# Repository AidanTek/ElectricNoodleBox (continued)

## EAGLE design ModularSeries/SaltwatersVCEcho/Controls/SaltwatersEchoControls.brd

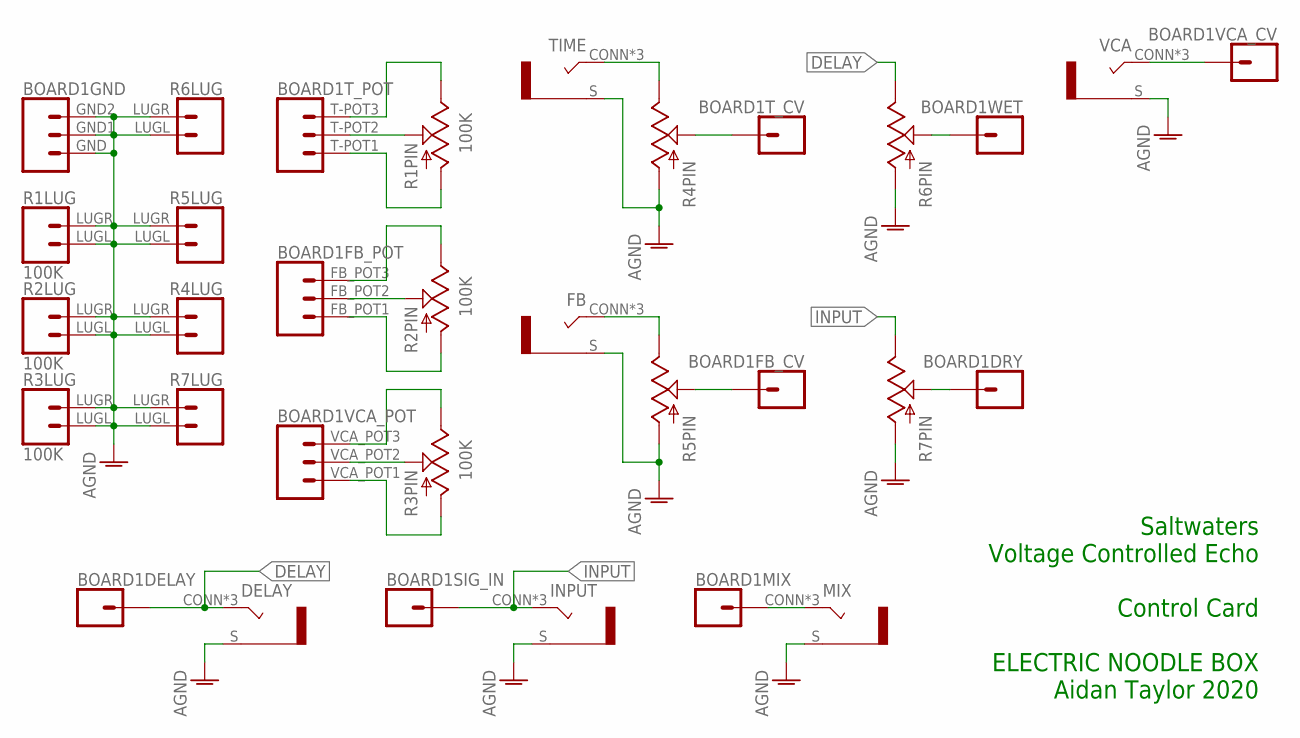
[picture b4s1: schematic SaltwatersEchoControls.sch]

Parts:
BOARD1: SALTWATERS_LINK; SALTWATERS
DELAY: COMBI-JACKCINCHNANA; NEWCOMBOJACK_PANEL
FB: COMBI-JACKCINCHNANA; NEWCOMBOJACK_PANEL
INPUT: COMBI-JACKCINCHNANA; NEWCOMBOJACK_PANEL
MIX: COMBI-JACKCINCHNANA; NEWCOMBOJACK_PANEL
R1, R2, R3: 100K; ALPHA_RV09_9MMPOT
R4, R5, R6, R7: POTENTIOMETER; ALPHA_RV09_9MMPOT
TIME: COMBI-JACKCINCHNANA; NEWCOMBOJACK_PANEL
VCA: COMBI-JACKCINCHNANA; NEWCOMBOJACK_PANEL

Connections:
AGND: BOARD1.GND (1), BOARD1.GND1 (2), BOARD1.GND2 (3), DELAY.S, FB.S, INPUT.S, MIX.S, R1.LUGL (1), R1.LUGR (2), R2.LUGL (1), R2.LUGR (2), R3.LUGL (1), R3.LUGR (2), R4.C1 (A), R4.LUGL (1), R4.LUGR (2), R5.C1 (A), R5.LUGL (1), R5.LUGR (2), R6.C1 (A), R6.LUGL (1), R6.LUGR (2), R7.C1 (A), R7.LUGL (1), R7.LUGR (2), TIME.S, VCA.S
DELAY: BOARD1.DELAY (1), DELAY.CONN (T), DELAY.T1 (T), DELAY.T2 (T), R6.C3 (B)
INPUT: BOARD1.SIG_IN (1), INPUT.CONN (T), INPUT.T1 (T), INPUT.T2 (T), R7.C3 (B)
unnamed: BOARD1.T-POT2 (2), R1.C2 (W)
unnamed: BOARD1.T-POT3 (3), R1.C3 (B)
unnamed: BOARD1.T-POT1 (1), R1.C1 (A)
unnamed: BOARD1.FB_POT2 (2), R2.C2 (W)
unnamed: BOARD1.FB_POT3 (3), R2.C3 (B)
unnamed: BOARD1.FB_POT1 (1), R2.C1 (A)
unnamed: BOARD1.VCA_POT2 (2), R3.C2 (W)
unnamed: BOARD1.VCA_POT3 (3), R3.C3 (B)
unnamed: BOARD1.VCA_POT1 (1), R3.C1 (A)
unnamed: R4.C3 (B), TIME.CONN (T), TIME.T1 (T), TIME.T2 (T)
unnamed: FB.CONN (T), FB.T1 (T), FB.T2 (T), R5.C3 (B)
unnamed: BOARD1.T_CV (1), R4.C2 (W)
unnamed: BOARD1.WET (1), R6.C2 (W)
unnamed: BOARD1.FB_CV (1), R5.C2 (W)
unnamed: BOARD1.DRY (1), R7.C2 (W)
unnamed: BOARD1.MIX (1), MIX.CONN (T), MIX.T1 (T), MIX.T2 (T)
unnamed: BOARD1.VCA_CV (1), VCA.CONN (T), VCA.T1 (T), VCA.T2 (T)

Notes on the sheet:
Saltwaters Voltage Controlled Echo Control Card ELECTRIC NOODLE BOX Aidan Taylor 2020

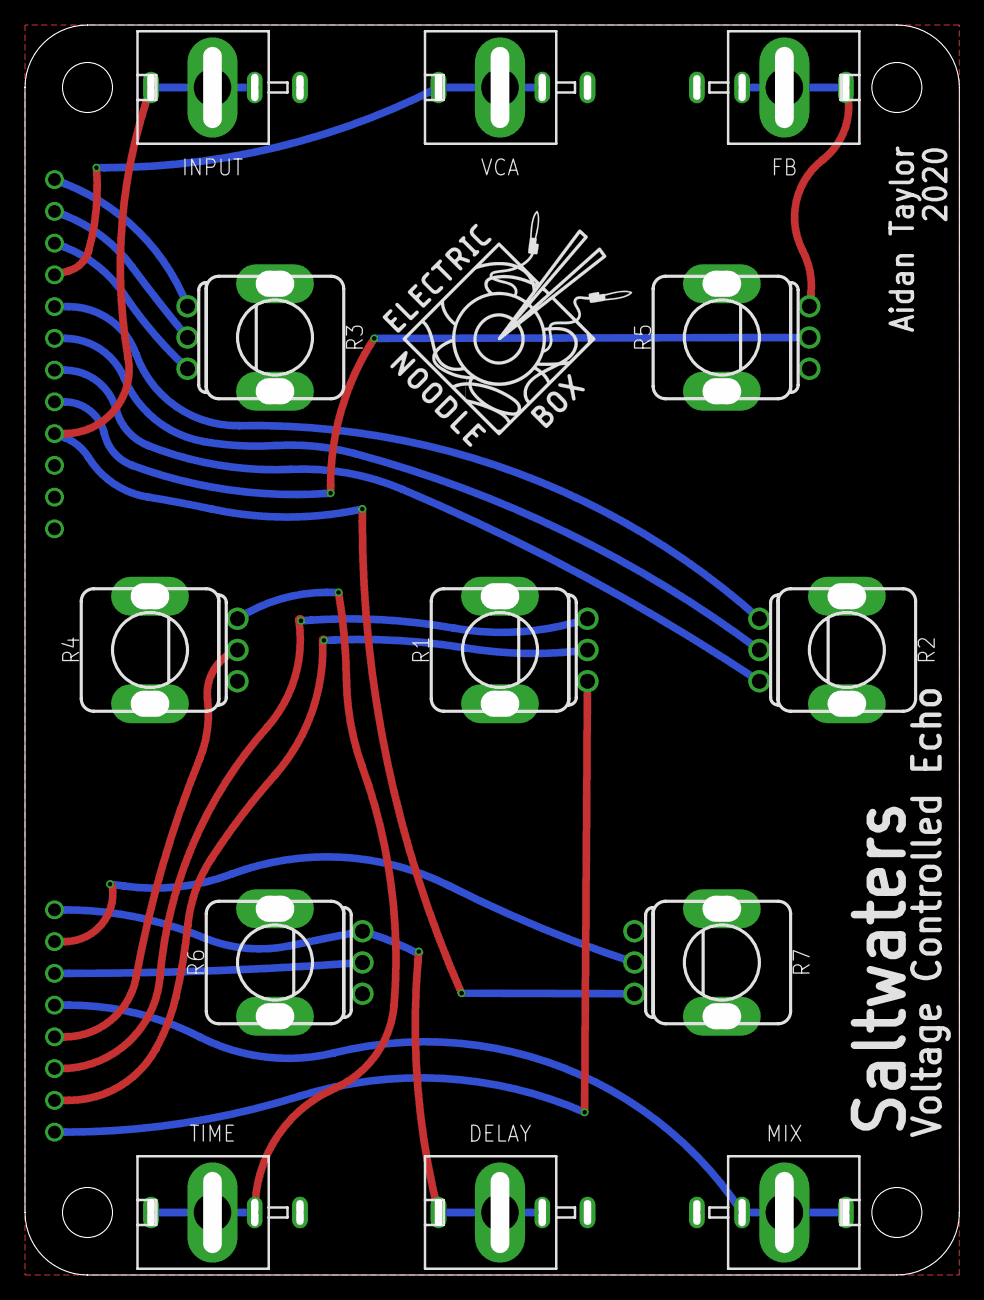
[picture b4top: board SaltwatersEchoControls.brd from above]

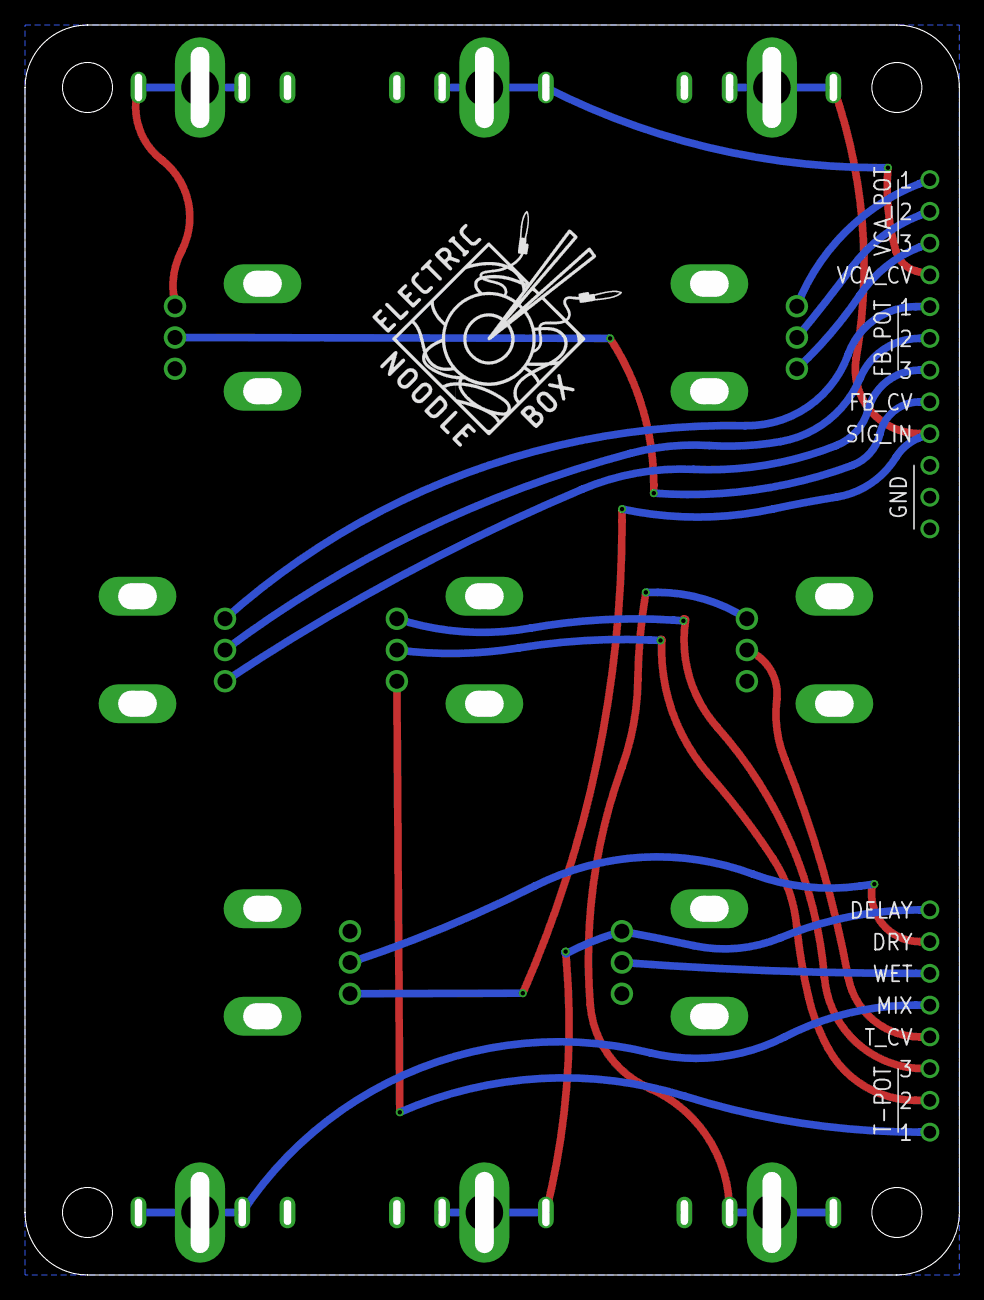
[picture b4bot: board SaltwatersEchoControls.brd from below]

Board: 2 copper layers, 74.8 x 100.0 mm, 16 parts (2 on the bottom side), 20 nets.

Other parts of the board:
U$1, U$2: LOGO20X20

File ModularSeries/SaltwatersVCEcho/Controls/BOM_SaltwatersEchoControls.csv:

"Qty";"Value";"Device";"Package";"Parts";"Description";"";
"4";"";"POTENTIOMETER";"ALPHA_RV09_9MMPOT";"R4, R5, R6, R7";"";"";
"3";"100K";"POTENTIOMETER";"ALPHA_RV09_9MMPOT";"R1, R2, R3";"";"";
"6";"COMBI-JACKCINCHNANA";"COMBI-JACKCINCHNANA";"NEWCOMBOJACK_PANEL";"DELAY, FB, INPUT, MIX, TIME, VCA";"";"";
"1";"SALTWATERS_LINK";"SALTWATERS_LINK";"SALTWATERS";"BOARD1";"";"";

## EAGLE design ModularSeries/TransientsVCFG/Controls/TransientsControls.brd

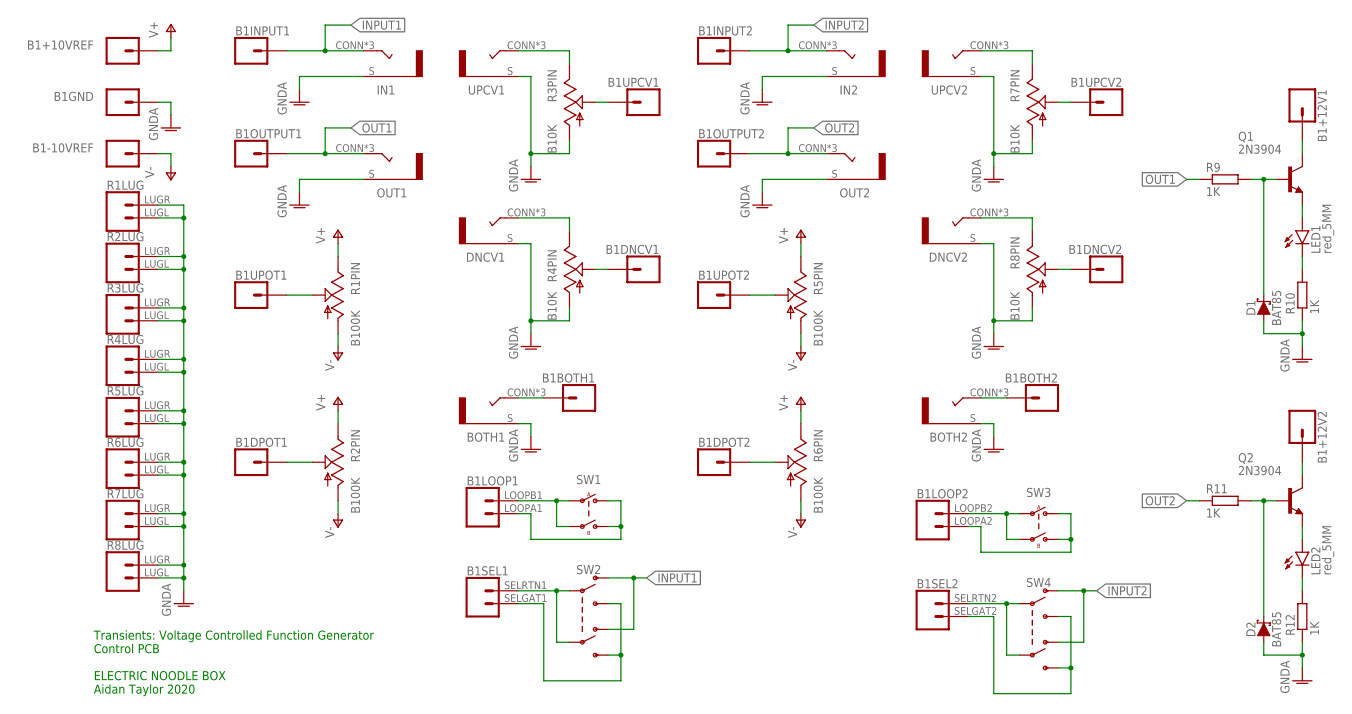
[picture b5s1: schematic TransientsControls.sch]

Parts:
B1: TRANSIENTS_LINK; TRANSIENTS
BOTH1, BOTH2: COMBI-JACKCINCHNANA; NEWCOMBOJACK_PANEL
D1, D2: BAT85; DO35-7
DNCV1, DNCV2: COMBI-JACKCINCHNANA; NEWCOMBOJACK_PANEL
IN1, IN2: COMBI-JACKCINCHNANA; NEWCOMBOJACK_PANEL
LED1, LED2: red_5MM; LED5MM
OUT1, OUT2: COMBI-JACKCINCHNANA; NEWCOMBOJACK_PANEL
Q1, Q2: 2N3904; TO92
R1, R2, R5, R6: B100K; ALPHA_RV09_9MMPOT
R3, R4, R7, R8: B10K; ALPHA_RV09_9MMPOT
R9, R10, R11, R12: 1K; 0207/10
SW1, SW3: PVA1_DPST; PVA1_PUSHBUTTON
SW2, SW4: PVA2_DPDT; PVA2_PUSHBUTTON
UPCV1, UPCV2: COMBI-JACKCINCHNANA; NEWCOMBOJACK_PANEL

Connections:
GNDA: B1.GND1 (1), B1.GND2 (1), BOTH1.S, BOTH2.S, D1.A, D2.A, DNCV1.S, DNCV2.S, IN1.S, IN2.S, OUT1.S, OUT2.S, R1.LUGL (1), R1.LUGR (2), R2.LUGL (1), R2.LUGR (2), R3.C1 (A), R3.LUGL (1), R3.LUGR (2), R4.C1 (A), R4.LUGL (1), R4.LUGR (2), R5.LUGL (1), R5.LUGR (2), R6.LUGL (1), R6.LUGR (2), R7.C1 (A), R7.LUGL (1), R7.LUGR (2), R8.C1 (A), R8.LUGL (1), R8.LUGR (2), R10.1, R12.1, UPCV1.S, UPCV2.S
INPUT1: B1.IN1 (1), IN1.CONN (T), IN1.T1 (T), IN1.T2 (T), SW2.SWA2 (SW1_3), SW2.SWB2 (SW2_3)
INPUT2: B1.INPUT2 (1), IN2.CONN (T), IN2.T1 (T), IN2.T2 (T), SW4.SWA2 (SW1_3), SW4.SWB2 (SW2_3)
unnamed: B1.+12V1 (1), Q1.1 (C)
unnamed: B1.UPOT1 (1), R1.C2 (W)
unnamed: B1.DPOT1 (1), R2.C2 (W)
unnamed: DNCV1.CONN (T), DNCV1.T1 (T), DNCV1.T2 (T), R4.C3 (B)
unnamed: R3.C3 (B), UPCV1.CONN (T), UPCV1.T1 (T), UPCV1.T2 (T)
unnamed: B1.UPCV1 (1), R3.C2 (W)
unnamed: B1.BOTH1 (1), BOTH1.CONN (T), BOTH1.T1 (T), BOTH1.T2 (T)
unnamed: B1.DNCV1 (1), R4.C2 (W)
unnamed: B1.UPOT2 (1), R5.C2 (W)
unnamed: B1.DPOT2 (1), R6.C2 (W)
unnamed: B1.LOOPB1 (2), SW1.SWA1, SW1.SWB1
unnamed: B1.LOOPA1 (1), SW1.SWA2, SW1.SWB2
unnamed: B1.SELGAT1 (1), SW2.SWA1 (SW1_1), SW2.SWB1 (SW2_1)
unnamed: B1.SELRTN1 (2), SW2.SWA0 (SW1_2), SW2.SWB0 (SW2_2)
unnamed: R7.C3 (B), UPCV2.CONN (T), UPCV2.T1 (T), UPCV2.T2 (T)
unnamed: B1.UPCV2 (1), R7.C2 (W)
unnamed: DNCV2.CONN (T), DNCV2.T1 (T), DNCV2.T2 (T), R8.C3 (B)
unnamed: B1.DNCV2 (1), R8.C2 (W)
unnamed: B1.BOTH2 (1), BOTH2.CONN (T), BOTH2.T1 (T), BOTH2.T2 (T)
unnamed: B1.LOOPB2 (2), SW3.SWA1, SW3.SWB1
unnamed: B1.LOOPA2 (1), SW3.SWA2, SW3.SWB2
unnamed: B1.SELGAT2 (1), SW4.SWA1 (SW1_1), SW4.SWB1 (SW2_1)
unnamed: B1.SELRTN2 (2), SW4.SWA0 (SW1_2), SW4.SWB0 (SW2_2)
unnamed: D1.C, Q1.2 (B), R9.2
unnamed: LED1.A, Q1.3 (E)
unnamed: LED1.K (C), R10.2
unnamed: D2.C, Q2.2 (B), R11.2
unnamed: LED2.A, Q2.3 (E)
unnamed: LED2.K (C), R12.2
unnamed: B1.+12V2 (1), Q2.1 (C)
OUT1: B1.OUT1 (1), OUT1.CONN (T), OUT1.T1 (T), OUT1.T2 (T), R9.1
OUT2: B1.OUT2 (1), OUT2.CONN (T), OUT2.T1 (T), OUT2.T2 (T), R11.1
V+: B1.+10VR1 (1), B1.+10VR2 (1), R1.C3 (B), R2.C3 (B), R5.C3 (B), R6.C3 (B)
V-: B1.-10VR1 (1), B1.-10VR2 (1), R1.C1 (A), R2.C1 (A), R5.C1 (A), R6.C1 (A)

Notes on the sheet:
Transients: Voltage Controlled Function Generator Control PCB ELECTRIC NOODLE BOX Aidan Taylor 2020

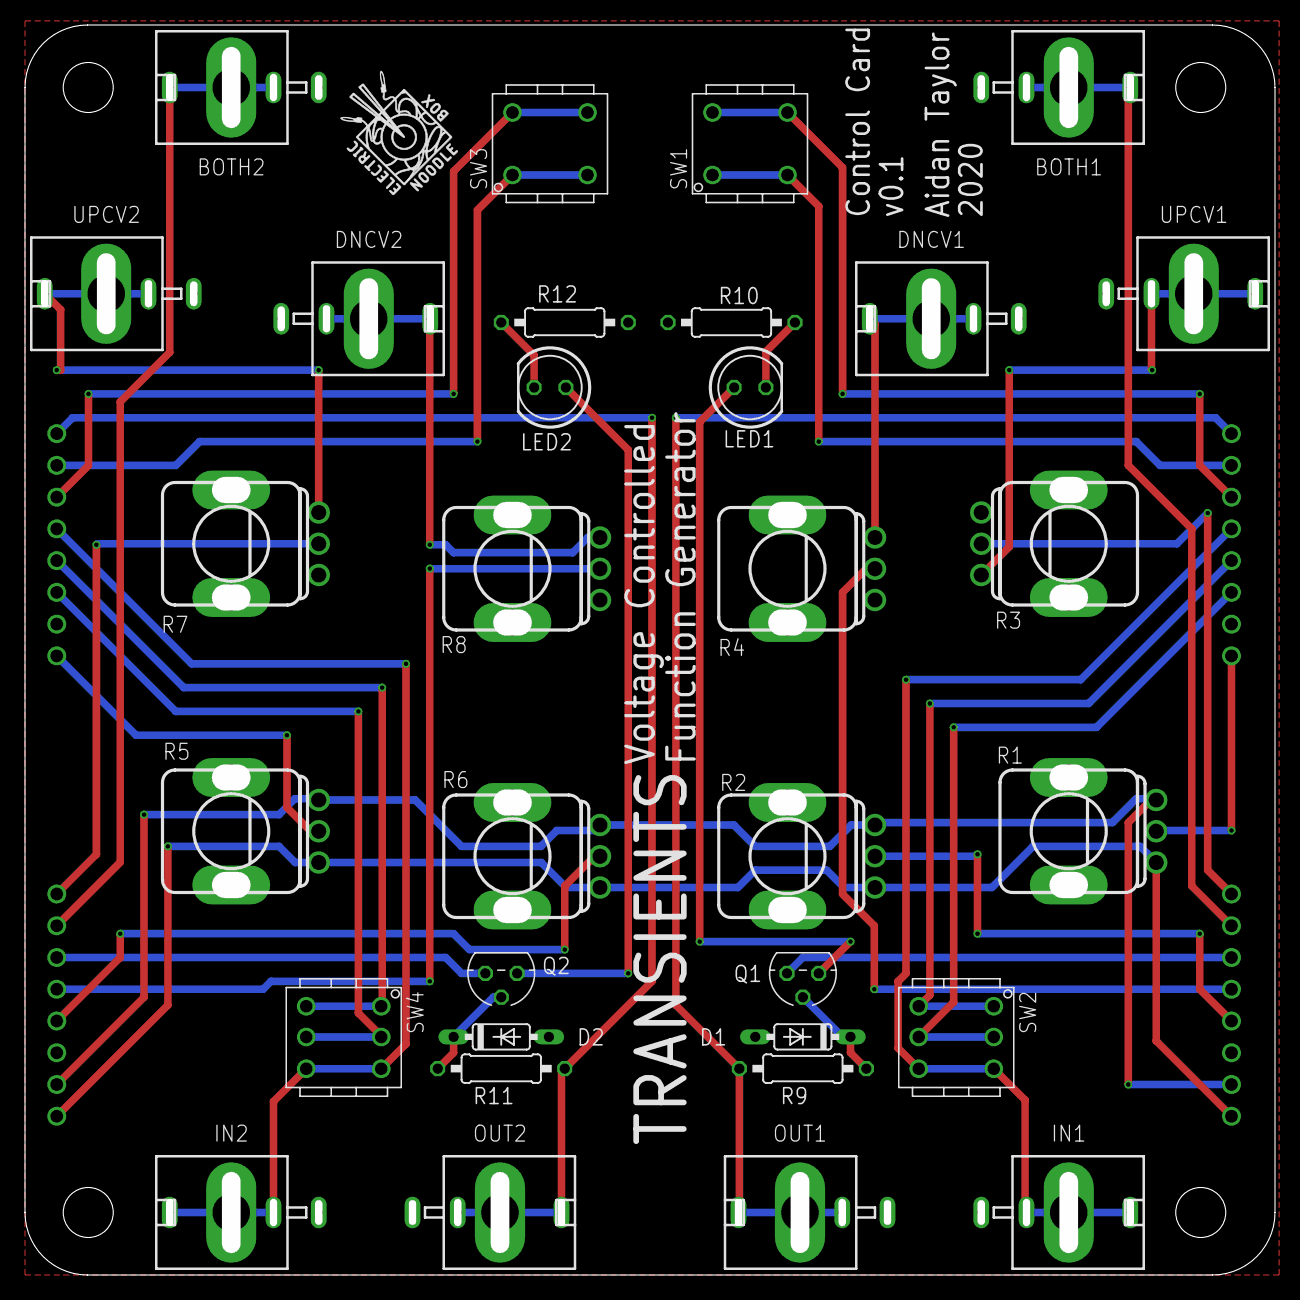
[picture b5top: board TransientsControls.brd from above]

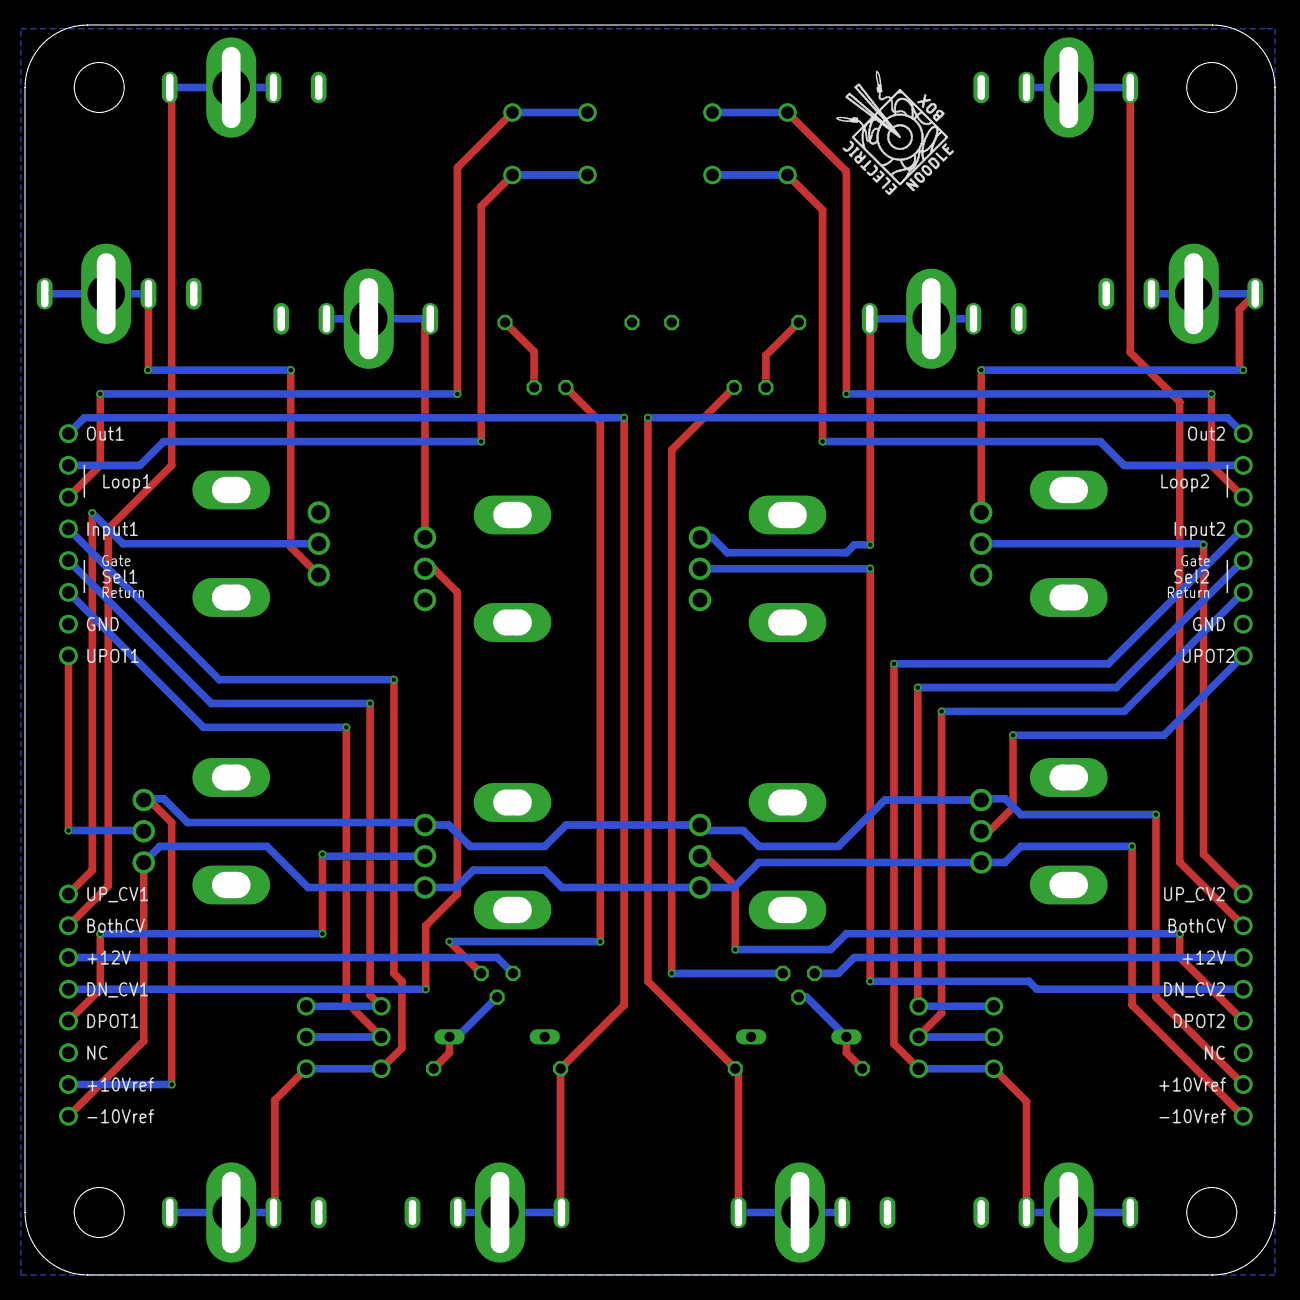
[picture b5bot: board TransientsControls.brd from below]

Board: 2 copper layers, 100.0 x 100.0 mm, 35 parts (2 on the bottom side), 37 nets.

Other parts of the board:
U$1, U$2: LOGO10X10

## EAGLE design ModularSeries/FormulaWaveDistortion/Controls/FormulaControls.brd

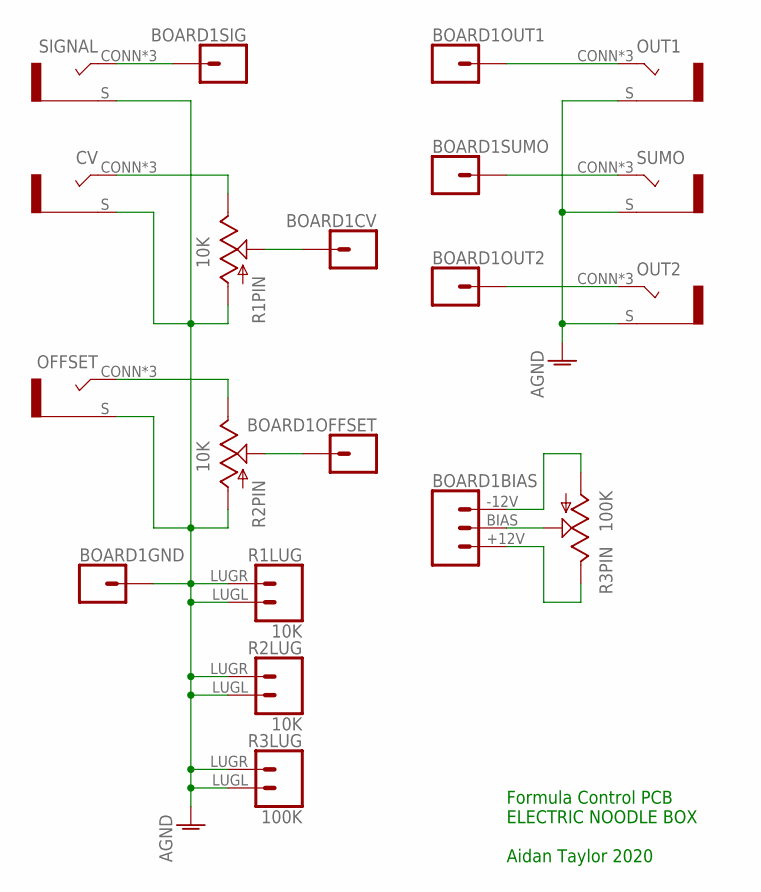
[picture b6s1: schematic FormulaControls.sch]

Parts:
BOARD1: FORMULA_LINK; FORMULA
CV: COMBI-JACKCINCHNANA; NEWCOMBOJACK_PANEL
OFFSET: COMBI-JACKCINCHNANA; NEWCOMBOJACK_PANEL
OUT1, OUT2: COMBI-JACKCINCHNANA; NEWCOMBOJACK_PANEL
R1, R2: 10K; ALPHA_RV09_9MMPOT
R3: 100K; ALPHA_RV09_9MMPOT
SIGNAL: COMBI-JACKCINCHNANA; NEWCOMBOJACK_PANEL
SUMO: COMBI-JACKCINCHNANA; NEWCOMBOJACK_PANEL

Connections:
AGND: BOARD1.GND (1), CV.S, OFFSET.S, OUT1.S, OUT2.S, R1.C1 (A), R1.LUGL (1), R1.LUGR (2), R2.C1 (A), R2.LUGL (1), R2.LUGR (2), R3.LUGL (1), R3.LUGR (2), SIGNAL.S, SUMO.S
unnamed: BOARD1.SIG (1), SIGNAL.CONN (T), SIGNAL.T1 (T), SIGNAL.T2 (T)
unnamed: CV.CONN (T), CV.T1 (T), CV.T2 (T), R1.C3 (B)
unnamed: BOARD1.OUT1 (1), OUT1.CONN (T), OUT1.T1 (T), OUT1.T2 (T)
unnamed: BOARD1.CV (1), R1.C2 (W)
unnamed: OFFSET.CONN (T), OFFSET.T1 (T), OFFSET.T2 (T), R2.C3 (B)
unnamed: BOARD1.BIAS (2), R3.C2 (W)
unnamed: BOARD1.OFFSET (1), R2.C2 (W)
unnamed: BOARD1.SUMO (1), SUMO.CONN (T), SUMO.T1 (T), SUMO.T2 (T)
unnamed: BOARD1.OUT2 (1), OUT2.CONN (T), OUT2.T1 (T), OUT2.T2 (T)
unnamed: BOARD1.-12V (3), R3.C1 (A)
unnamed: BOARD1.+12V (1), R3.C3 (B)

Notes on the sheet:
Formula Control PCB ELECTRIC NOODLE BOX Aidan Taylor 2020

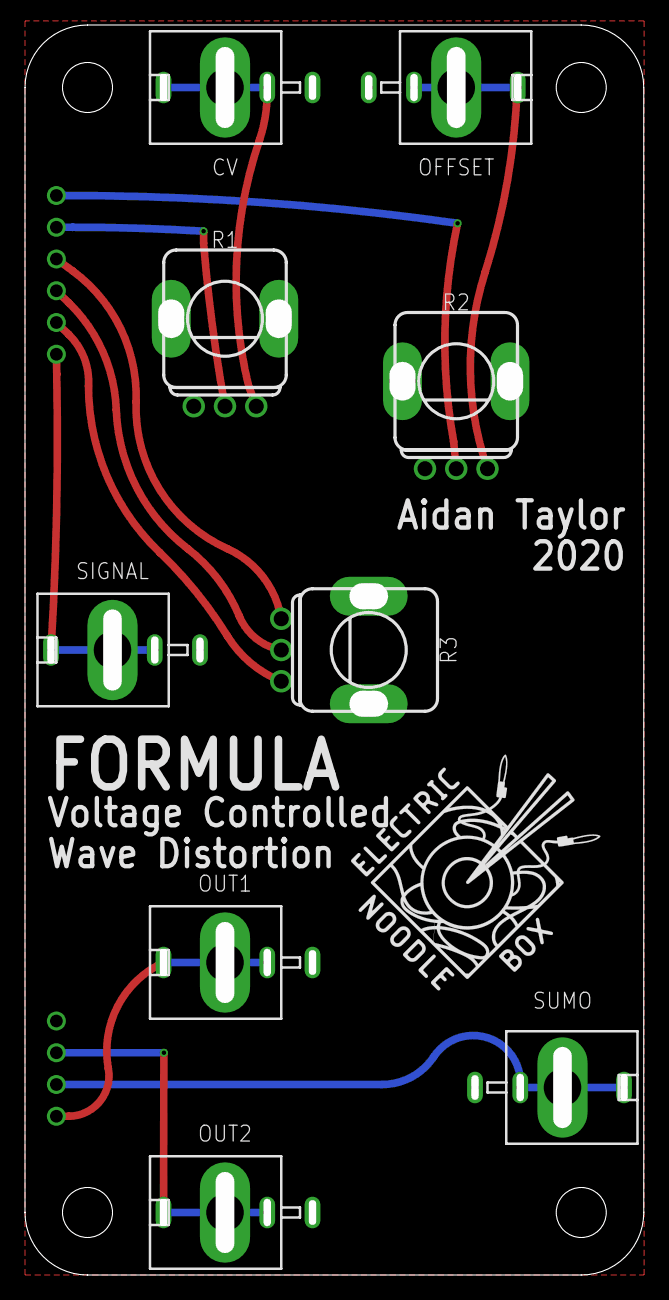
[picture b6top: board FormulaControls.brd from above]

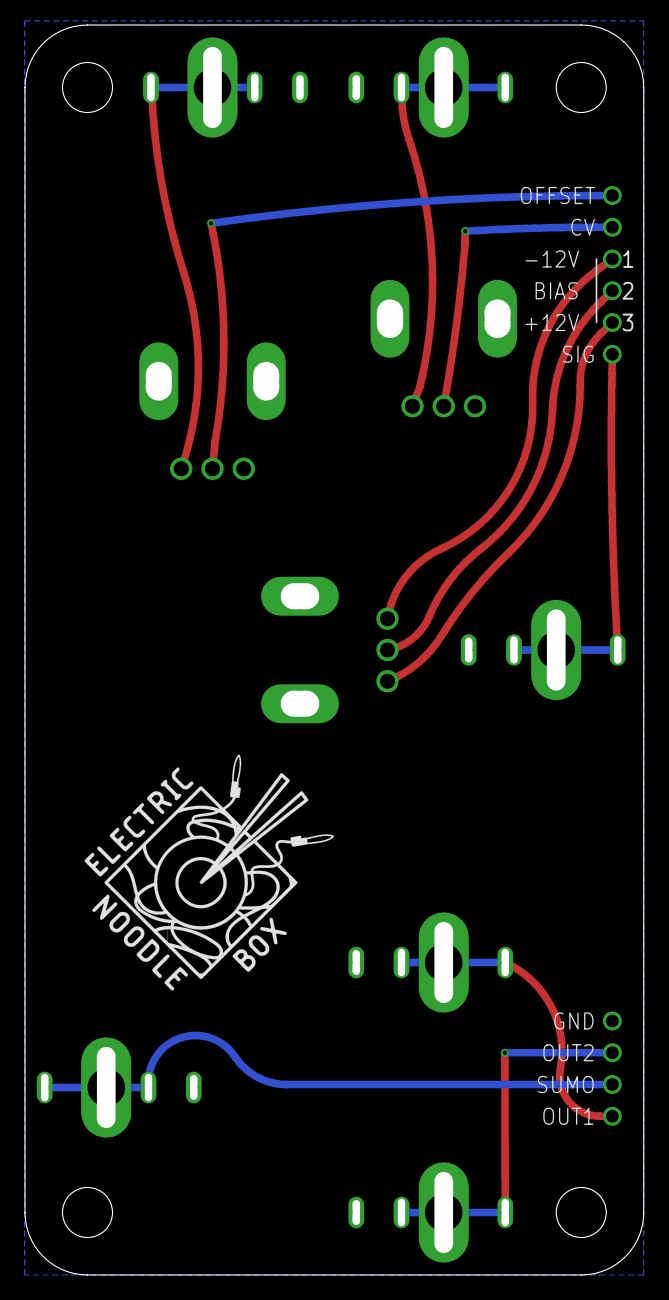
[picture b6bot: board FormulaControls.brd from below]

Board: 2 copper layers, 49.5 x 100.0 mm, 12 parts (2 on the bottom side), 12 nets.

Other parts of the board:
U$1, U$2: LOGO20X20

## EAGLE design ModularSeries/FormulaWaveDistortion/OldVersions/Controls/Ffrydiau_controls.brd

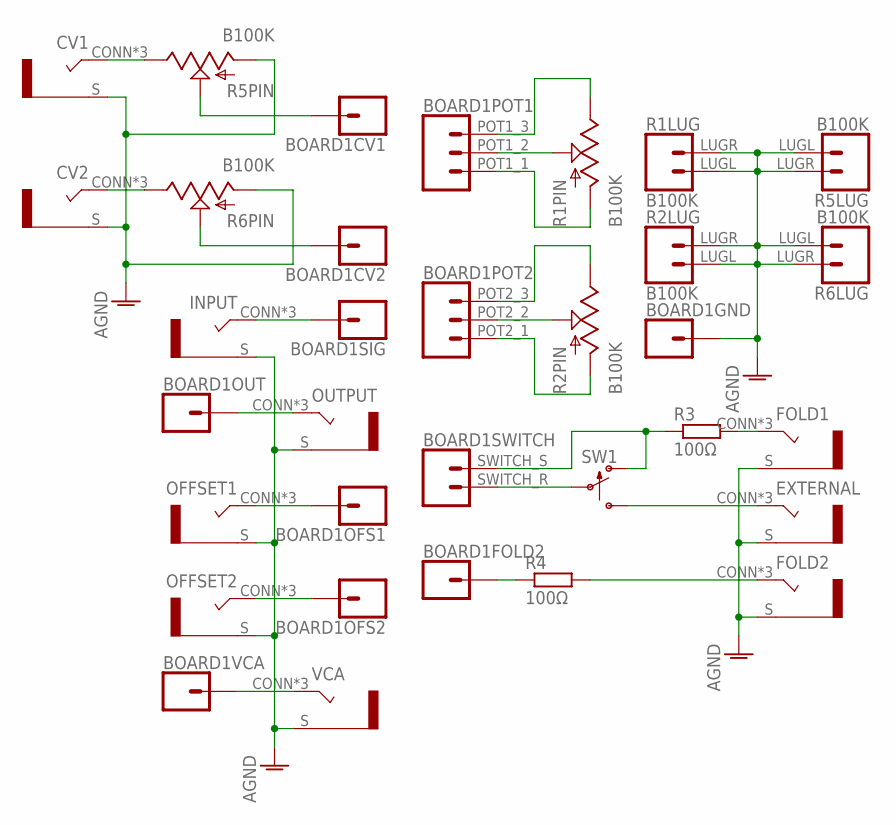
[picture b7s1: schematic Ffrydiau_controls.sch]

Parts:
BOARD1: FFRYDIAU_LINK; FFRYDIAU
CV1, CV2: COMBI-JACKCINCHNANA; NEWCOMBOJACK_PANEL
EXTERNAL: COMBI-JACKCINCHNANA; NEWCOMBOJACK_PANEL
FOLD1, FOLD2: COMBI-JACKCINCHNANA; NEWCOMBOJACK_PANEL
INPUT: COMBI-JACKCINCHNANA; NEWCOMBOJACK_PANEL
OFFSET1, OFFSET2: COMBI-JACKCINCHNANA; NEWCOMBOJACK_PANEL
OUTPUT: COMBI-JACKCINCHNANA; NEWCOMBOJACK_PANEL
R1, R2, R5, R6: B100K; ALPHA_RV09_9MMPOT
R3, R4: 100Ω; 0207/10
SW1: SPDT_SWITCHDW1; MICRODPDT-DW1
VCA: COMBI-JACKCINCHNANA; NEWCOMBOJACK_PANEL

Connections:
AGND: BOARD1.GND (1), CV1.S, CV2.S, EXTERNAL.S, FOLD1.S, FOLD2.S, INPUT.S, OFFSET1.S, OFFSET2.S, OUTPUT.S, R1.LUGL (1), R1.LUGR (2), R2.LUGL (1), R2.LUGR (2), R5.C1 (A), R5.LUGL (1), R5.LUGR (2), R6.C1 (A), R6.LUGL (1), R6.LUGR (2), VCA.S
unnamed: CV1.CONN (T), CV1.T1 (T), CV1.T2 (T), R5.C3 (B)
unnamed: BOARD1.CV1 (1), R5.C2 (W)
unnamed: BOARD1.SIG (1), INPUT.CONN (T), INPUT.T1 (T), INPUT.T2 (T)
unnamed: BOARD1.OUT (1), OUTPUT.CONN (T), OUTPUT.T1 (T), OUTPUT.T2 (T)
unnamed: BOARD1.POT1_2 (2), R1.C2 (W)
unnamed: BOARD1.OFS1 (1), OFFSET1.CONN (T), OFFSET1.T1 (T), OFFSET1.T2 (T)
unnamed: BOARD1.OFS2 (1), OFFSET2.CONN (T), OFFSET2.T1 (T), OFFSET2.T2 (T)
unnamed: BOARD1.VCA (1), VCA.CONN (T), VCA.T1 (T), VCA.T2 (T)
unnamed: BOARD1.POT1_1 (1), R1.C1 (A)
unnamed: BOARD1.POT1_3 (3), R1.C3 (B)
unnamed: BOARD1.POT2_2 (2), R2.C2 (W)
unnamed: BOARD1.POT2_3 (3), R2.C3 (B)
unnamed: BOARD1.POT2_1 (1), R2.C1 (A)
unnamed: BOARD1.SWITCH_S (2), R3.1, SW1.C1 (O)
unnamed: FOLD1.CONN (T), FOLD1.T1 (T), FOLD1.T2 (T), R3.2
unnamed: BOARD1.SWITCH_R (1), SW1.C2
unnamed: EXTERNAL.CONN (T), EXTERNAL.T1 (T), EXTERNAL.T2 (T), SW1.C3 (S)
unnamed: BOARD1.FOLD2 (1), R4.1
unnamed: FOLD2.CONN (T), FOLD2.T1 (T), FOLD2.T2 (T), R4.2
unnamed: CV2.CONN (T), CV2.T1 (T), CV2.T2 (T), R6.C3 (B)
unnamed: BOARD1.CV2 (1), R6.C2 (W)

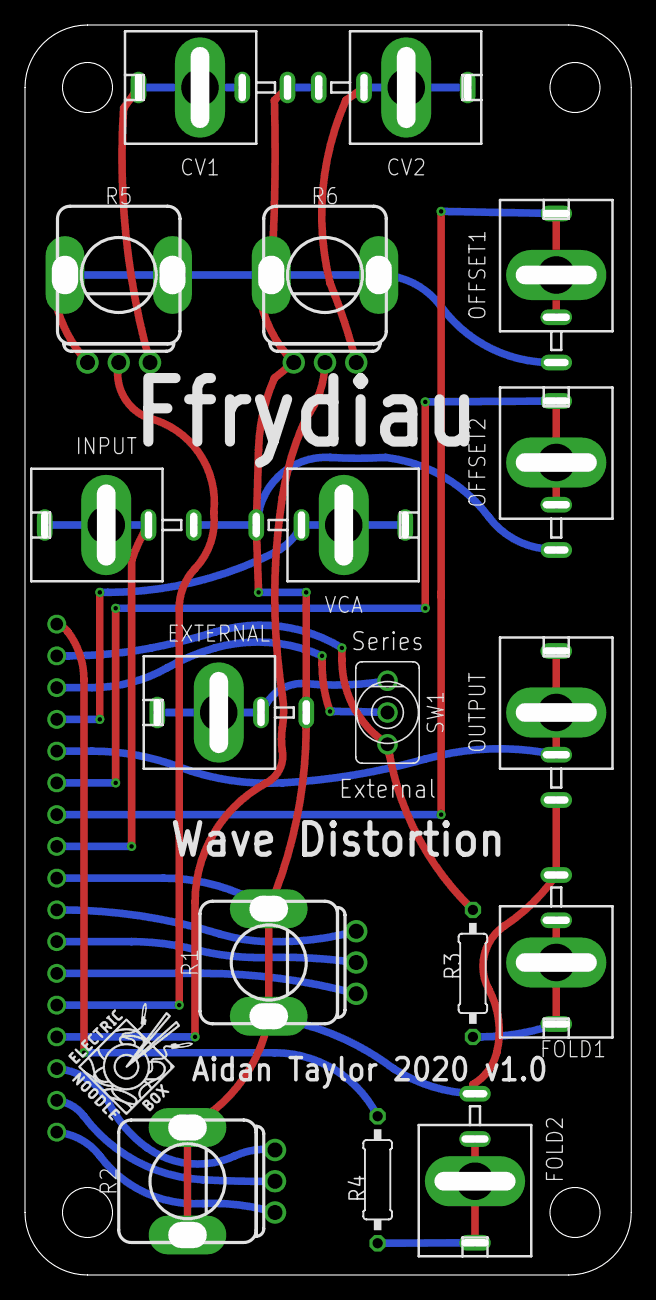
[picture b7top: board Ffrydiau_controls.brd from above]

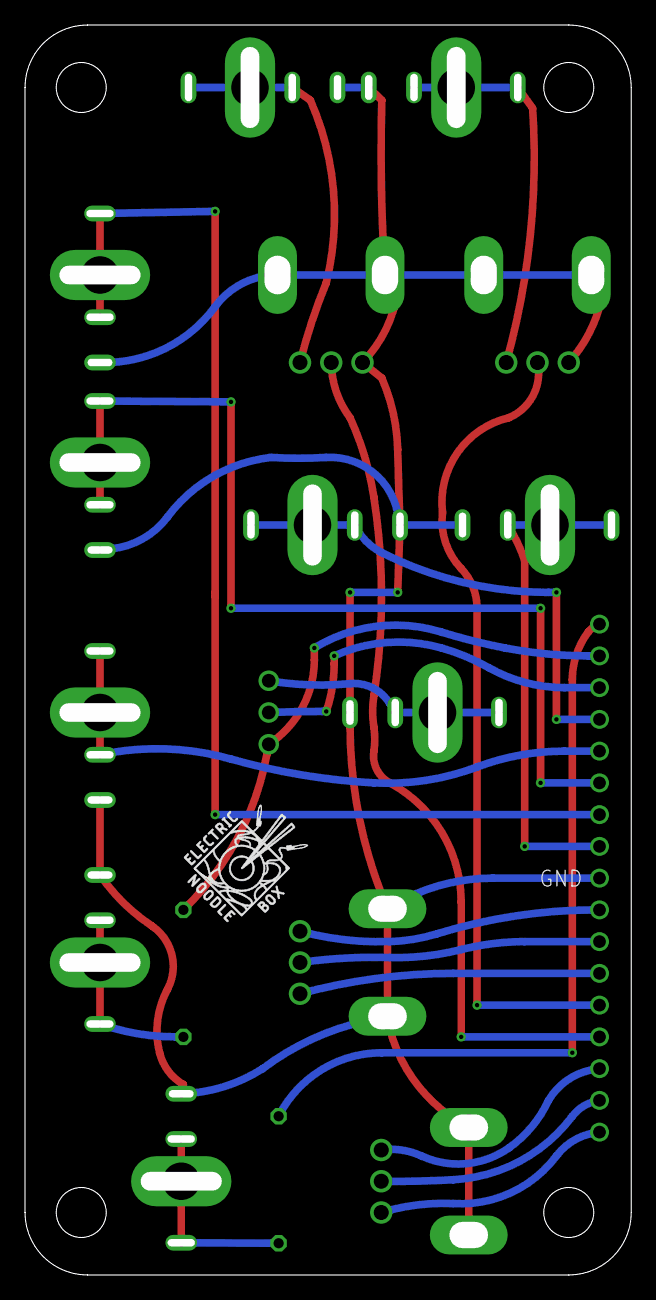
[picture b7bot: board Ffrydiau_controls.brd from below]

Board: 2 copper layers, 48.5 x 100.0 mm, 20 parts (2 on the bottom side), 22 nets.

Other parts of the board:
U$1, U$2: LOGO10X10

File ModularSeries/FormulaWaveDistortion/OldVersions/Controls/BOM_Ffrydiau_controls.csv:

Qty,Value,Package,Parts,Description,RETAILER,CATALOGUE
2,100Ω,0207/10,"R3, R4",RESISTOR 1/4W,Farnell,2329854
4,B100K,ALPHA_RV09_9MMPOT,"R1, R2, R5, R6",Taiwan Alpha 9mm Potentiometer,Thonk,D-shaft B100K
4,BANANA_PANEL,Cinch Banana Jack,"FOLD1, FOLD2, OUTPUT, VCA",Cinch Blue Banana Socket,Mouser,530-108-0910-1
4,BANANA_PANEL,Cinch Banana Jack,"CV1, CV2, OFFSET1, OFFSET2",Cinch Red Banana Socket,Mouser,530-108-0902-1
2,BANANA_PANEL,Cinch Banana Jack,"EXTERNAL, INPUT",Cinch Orange Banana Socket,Mouser,530-108-0906-1
1,SPDT_SWITCHDW1,MICRODPDT-DW1,SW1,SPDT Dailywell Toggle Switch,Thonk,DW1
4,Small Knob,Small Knob,"R1, R2, R5, R6",SIFAM/SELCO Small Black,Thonk,Small Black
2,Small Red Cap,Small Red Cap,"R5, R6",SIFAM/SELCO Cap Red Small,Thonk,Cap Small Red
2,Small Blue Cap,Small Blue Cap,"R1, R2",SIFAM/SELCO Cap Blue Small,Thonk,Cap Small Blue
3,Pin Header,Pin Header,,8way 1row 2.54mm Header Pin,Farnell,2856626
3,Socket Header,Socket Header,,8way 1row 2.54mm Header Socket,Farnell,1668208
4,PCB Standoff,PCB Standoff,,PCB Standoff M3,Farnell,1466945
4,M3 Screw,M3 Screw,,Stainless Steel M3,Farnell,1420032

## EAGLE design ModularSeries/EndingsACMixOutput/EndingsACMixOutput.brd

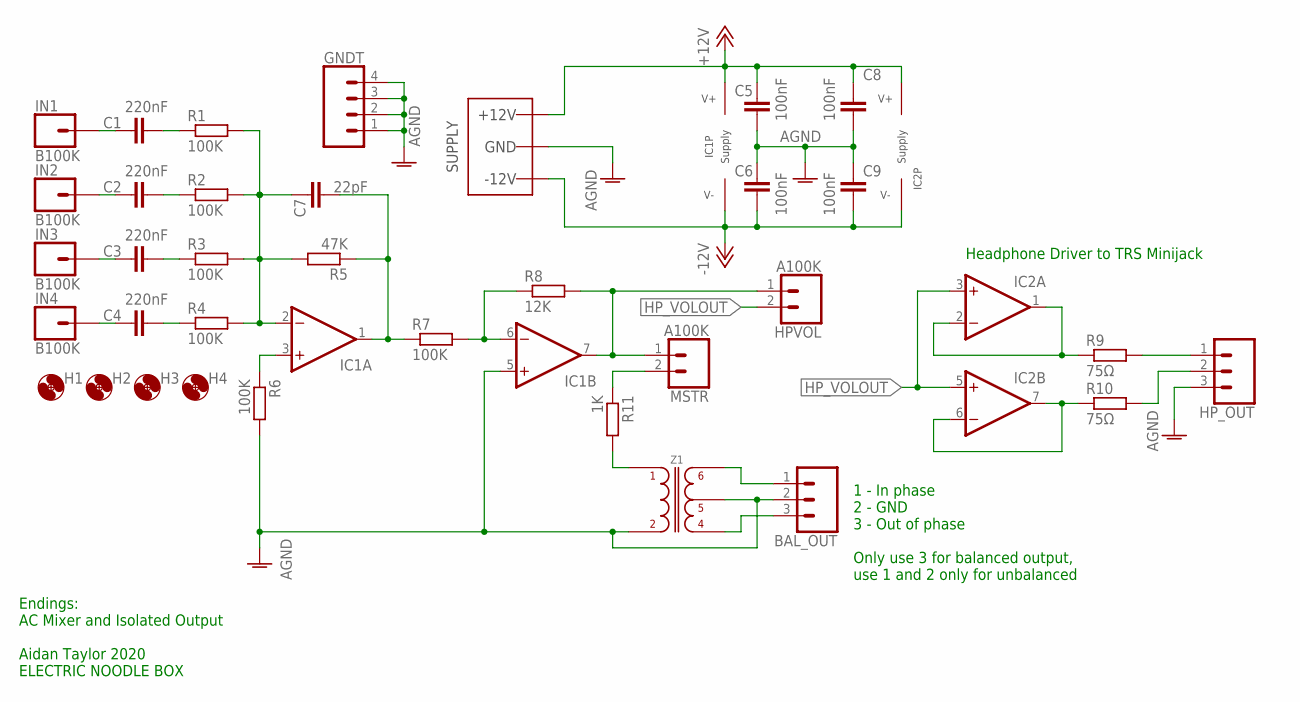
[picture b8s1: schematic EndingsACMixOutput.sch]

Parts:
BAL_OUT: 3XWIREPAD; 1X03
C1, C2, C3, C4: 220nF; C050-025X075
C5, C6, C8, C9: 100nF; C050-025X075
C7: 22pF; C050-025X075
GNDT: 4XWIREPAD; 1X04
H1, H2, H3, H4: MOUNT-HOLE3.2; 3,2
HPVOL: A100K; 1X02
HP_OUT: 3XWIREPAD; 1X03
IC1, IC2: TL0X2DIL; DIL08
IN1, IN2, IN3, IN4: B100K; 1X01
MSTR: A100K; 1X02
R1, R2, R3, R4, R6, R7: 100K; 0207/10
R5: 47K; 0207/10
R8: 12K; 0207/10
R9, R10: 75Ω; 0207/10
R11: 1K; 0207/10
WP1: COMBO_SUPPLY_HEADER; COMBINED_POWER
Z1: Z1604_AUDIO_TRANSFORMER; Z1604_TRANSFORMER

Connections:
+12V: C5.1, C8.1, IC1.8 (V+), IC2.8 (V+), WP1.V+1 (V++), WP1.V+2 (V++), WP1.V+3 (V++)
-12V: C6.2, C9.2, IC1.4 (V-), IC2.4 (V-), WP1.V-1 (V--), WP1.V-2 (V--), WP1.V-3 (V--)
AGND: BAL_OUT.2, C5.2, C6.1, C8.2, C9.1, GNDT.1, GNDT.2, GNDT.3, GNDT.4, HP_OUT.3, IC1.5 (+IN), R6.2, WP1.GND1 (AGND), WP1.GND2 (AGND), WP1.GND3 (AGND), WP1.GND4 (AGND), WP1.GND5 (AGND), WP1.GND6 (AGND), WP1.GND7 (AGND), WP1.GND8 (AGND), Z1.T3 (3), Z1.T5 (5)
HP_VOLOUT: HPVOL.2, IC2.3 (+IN), IC2.5 (+IN)
unnamed: C4.1, IN4.1
unnamed: C7.1, IC1.2 (-IN), R1.2, R2.2, R3.2, R4.2, R5.2
unnamed: C7.2, IC1.1 (OUT), R5.1, R7.1
unnamed: IC1.6 (-IN), R7.2, R8.1
unnamed: HPVOL.1, IC1.7 (OUT), MSTR.1, R8.2
unnamed: C3.1, IN3.1
unnamed: IC1.3 (+IN), R6.1
unnamed: C1.2, R1.1
unnamed: C2.2, R2.1
unnamed: C3.2, R3.1
unnamed: C4.2, R4.1
unnamed: C2.1, IN2.1
unnamed: C1.1, IN1.1
unnamed: MSTR.2, R11.1
unnamed: BAL_OUT.1, Z1.T6 (6)
unnamed: BAL_OUT.3, Z1.T4 (4)
unnamed: IC2.1 (OUT), IC2.2 (-IN), R9.1
unnamed: HP_OUT.1, R9.2
unnamed: IC2.6 (-IN), IC2.7 (OUT), R10.1
unnamed: HP_OUT.2, R10.2
unnamed: R11.2, Z1.T1 (1)

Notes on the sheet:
Endings: AC Mixer and Isolated Output Aidan Taylor 2020 ELECTRIC NOODLE BOX
Headphone Driver to TRS Minijack
1 - In phase 2 - GND 3 - Out of phase Only use 3 for balanced output, use 1 and 2 only for unbalanced

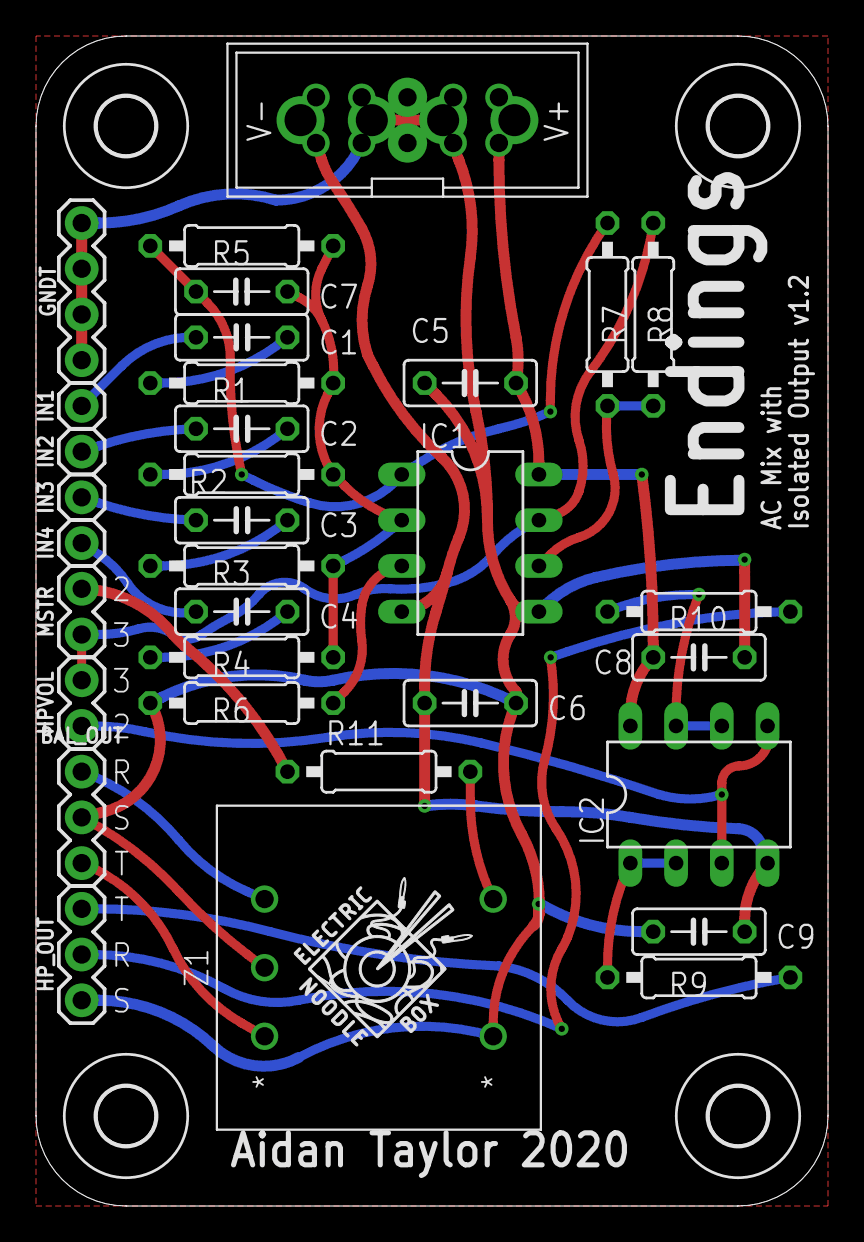
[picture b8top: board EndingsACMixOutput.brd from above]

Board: 2 copper layers, 44.0 x 65.0 mm, 39 parts (1 on the bottom side), 25 nets.

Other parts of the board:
U$1, U$2: LOGO10X10

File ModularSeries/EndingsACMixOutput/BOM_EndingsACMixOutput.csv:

Qty,Value,Package,Parts,Description,Retailer,Catalogue
,,,,,,
6,100K,0207/10,"R1, R2, R3, R4, R6, R7",RESISTOR 1/4W,Farnell,2329853
1,12K,0207/10,R8,RESISTOR 1/4W,Farnell,2329863
1,1K,0207/10,R11,RESISTOR 1/4W,Farnell,2329885
1,47K,0207/10,R5,RESISTOR 1/4W,Farnell,2329944
2,75Ω,0207/10,"R9, R10",RESISTOR 1/4W,Farnell,
,,,,,,
4,100nF,C050-025X075,"C5, C6, C8, C9",CAPACITOR,Farnell,2797801
4,220nF,C050-025X075,"C1, C2, C3, C4",CAPACITOR,Farnell,1679404
1,22pF,C050-025X075,C7,CAPACITOR,Farnell,1457695
,,,,,,
1,600:600 ,Z1604_TRANSFORMER,Z1,Z1604 Audio Transformer,Farnell,1172421
,,,,,,
2,NE5532,DIL08,"IC1, IC2",Low Noise Op-Amp 8-pin DIP,Farnell,3117314
,,,,,,
1,Power Header,,WP1,4 way MTA156 or 10 way IDC,Farnell,589068
1,(Alt) Power Header,,WP1,10 way Shrouded IDC,Farnell,2843527
,,,,,,
1,"TRS 1/4"" Jack","TRS 1/4"" Jack",OUT,"1/4"" Stereo Jack (panel part)",Farnell,4169190
1,TRS mini-jack,TRS mini-jack,HP_OUT,Stereo Jack (panel part),Farnell,2911026
2,A100K,,"HPVOL, MSTR",Taiwan Alpha 16mm (panel part),Rapid,65-0830
4,B100K,,"IN1, IN2, IN3, IN4",Taiwan Alpha 16mm (panel part),Rapid,65-0756
4,Orange Banana,,"IN1, IN2, IN3, IN4",Johnson/Cinch Banana Orange (panel part),Mouser,530-108-0906-1
